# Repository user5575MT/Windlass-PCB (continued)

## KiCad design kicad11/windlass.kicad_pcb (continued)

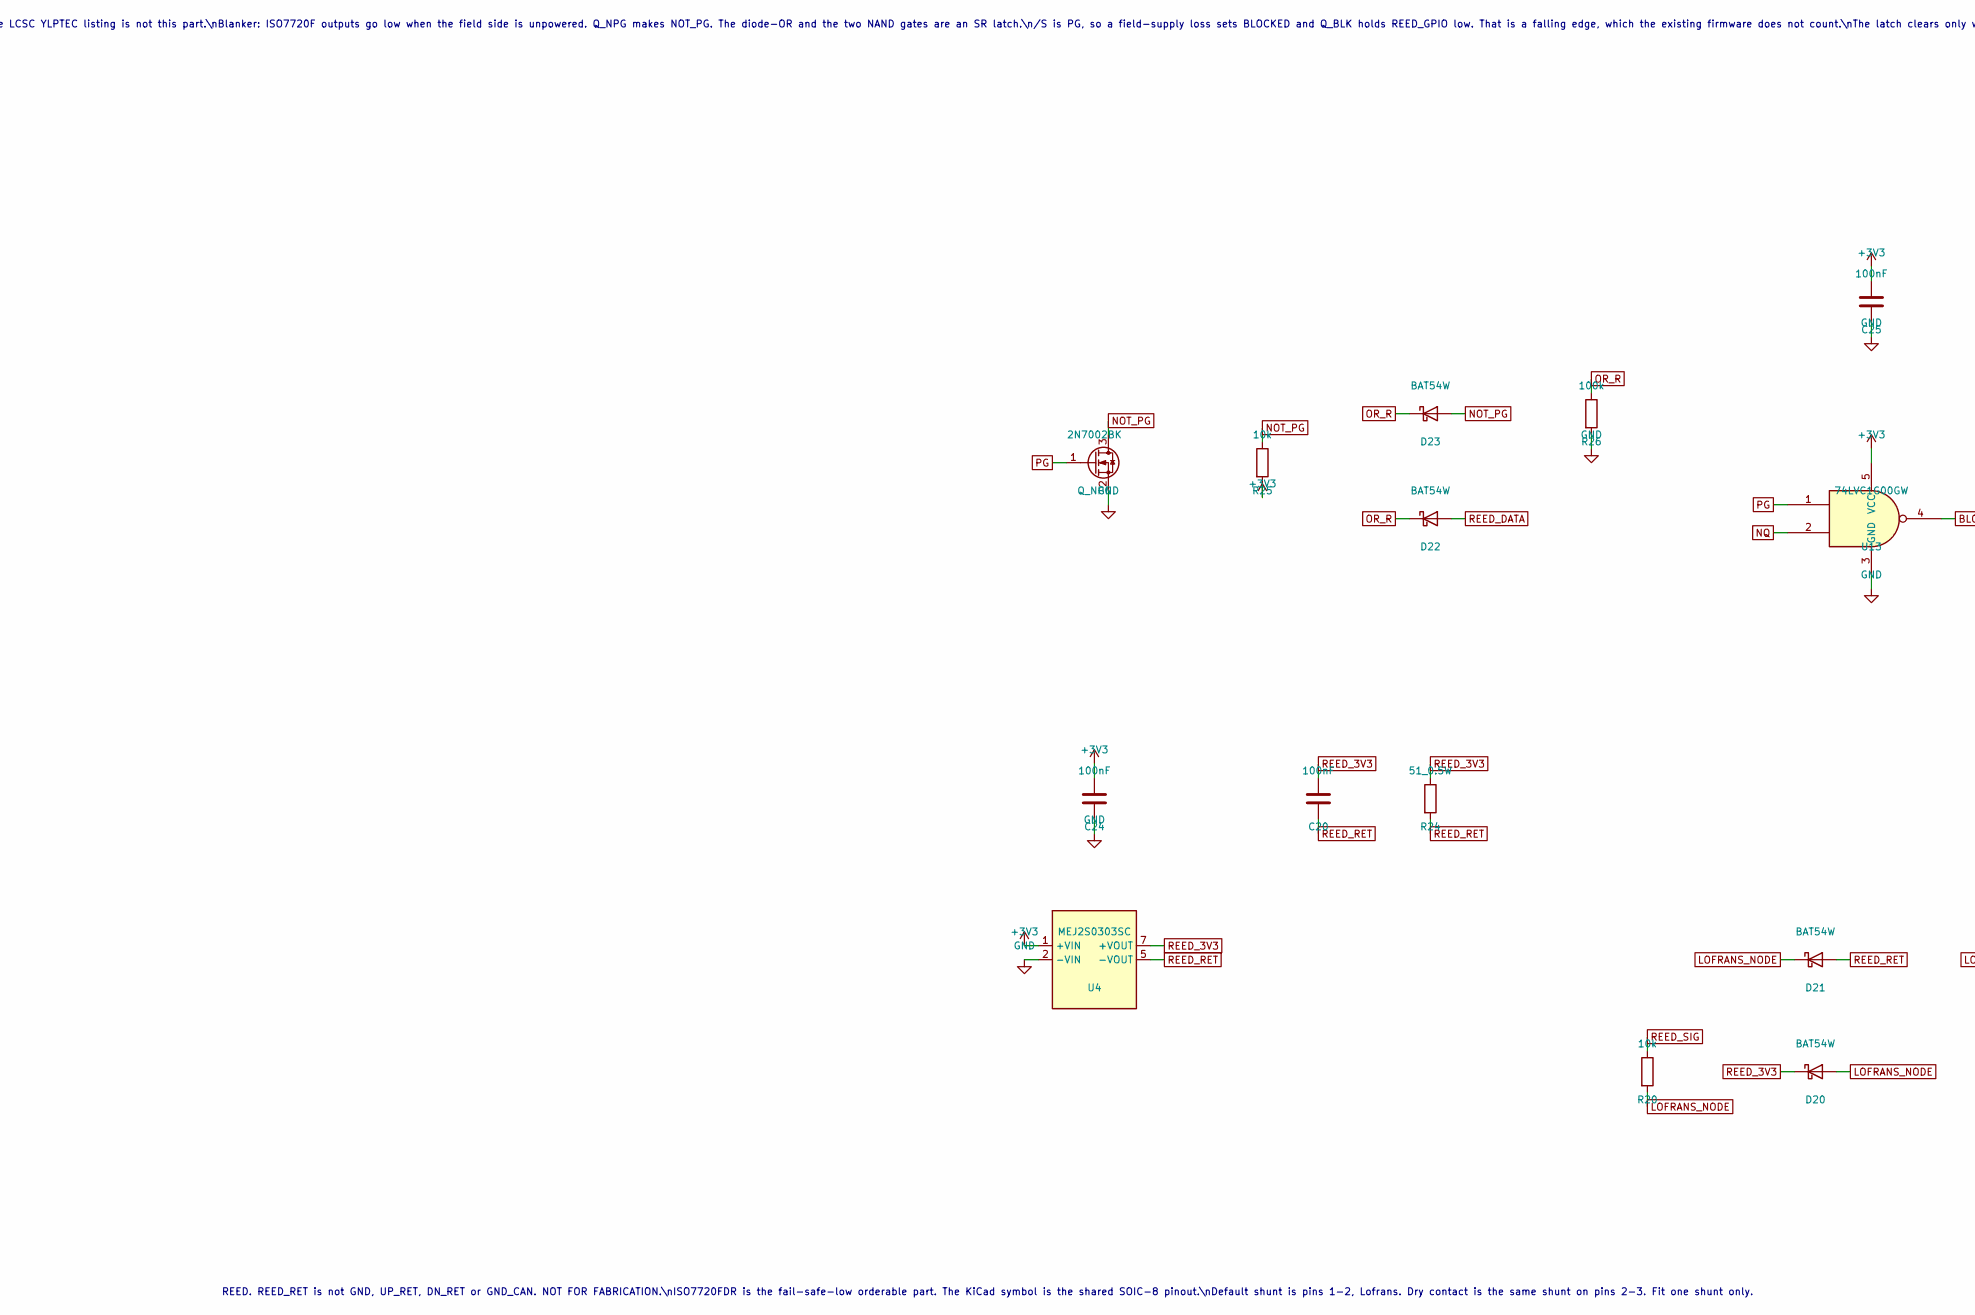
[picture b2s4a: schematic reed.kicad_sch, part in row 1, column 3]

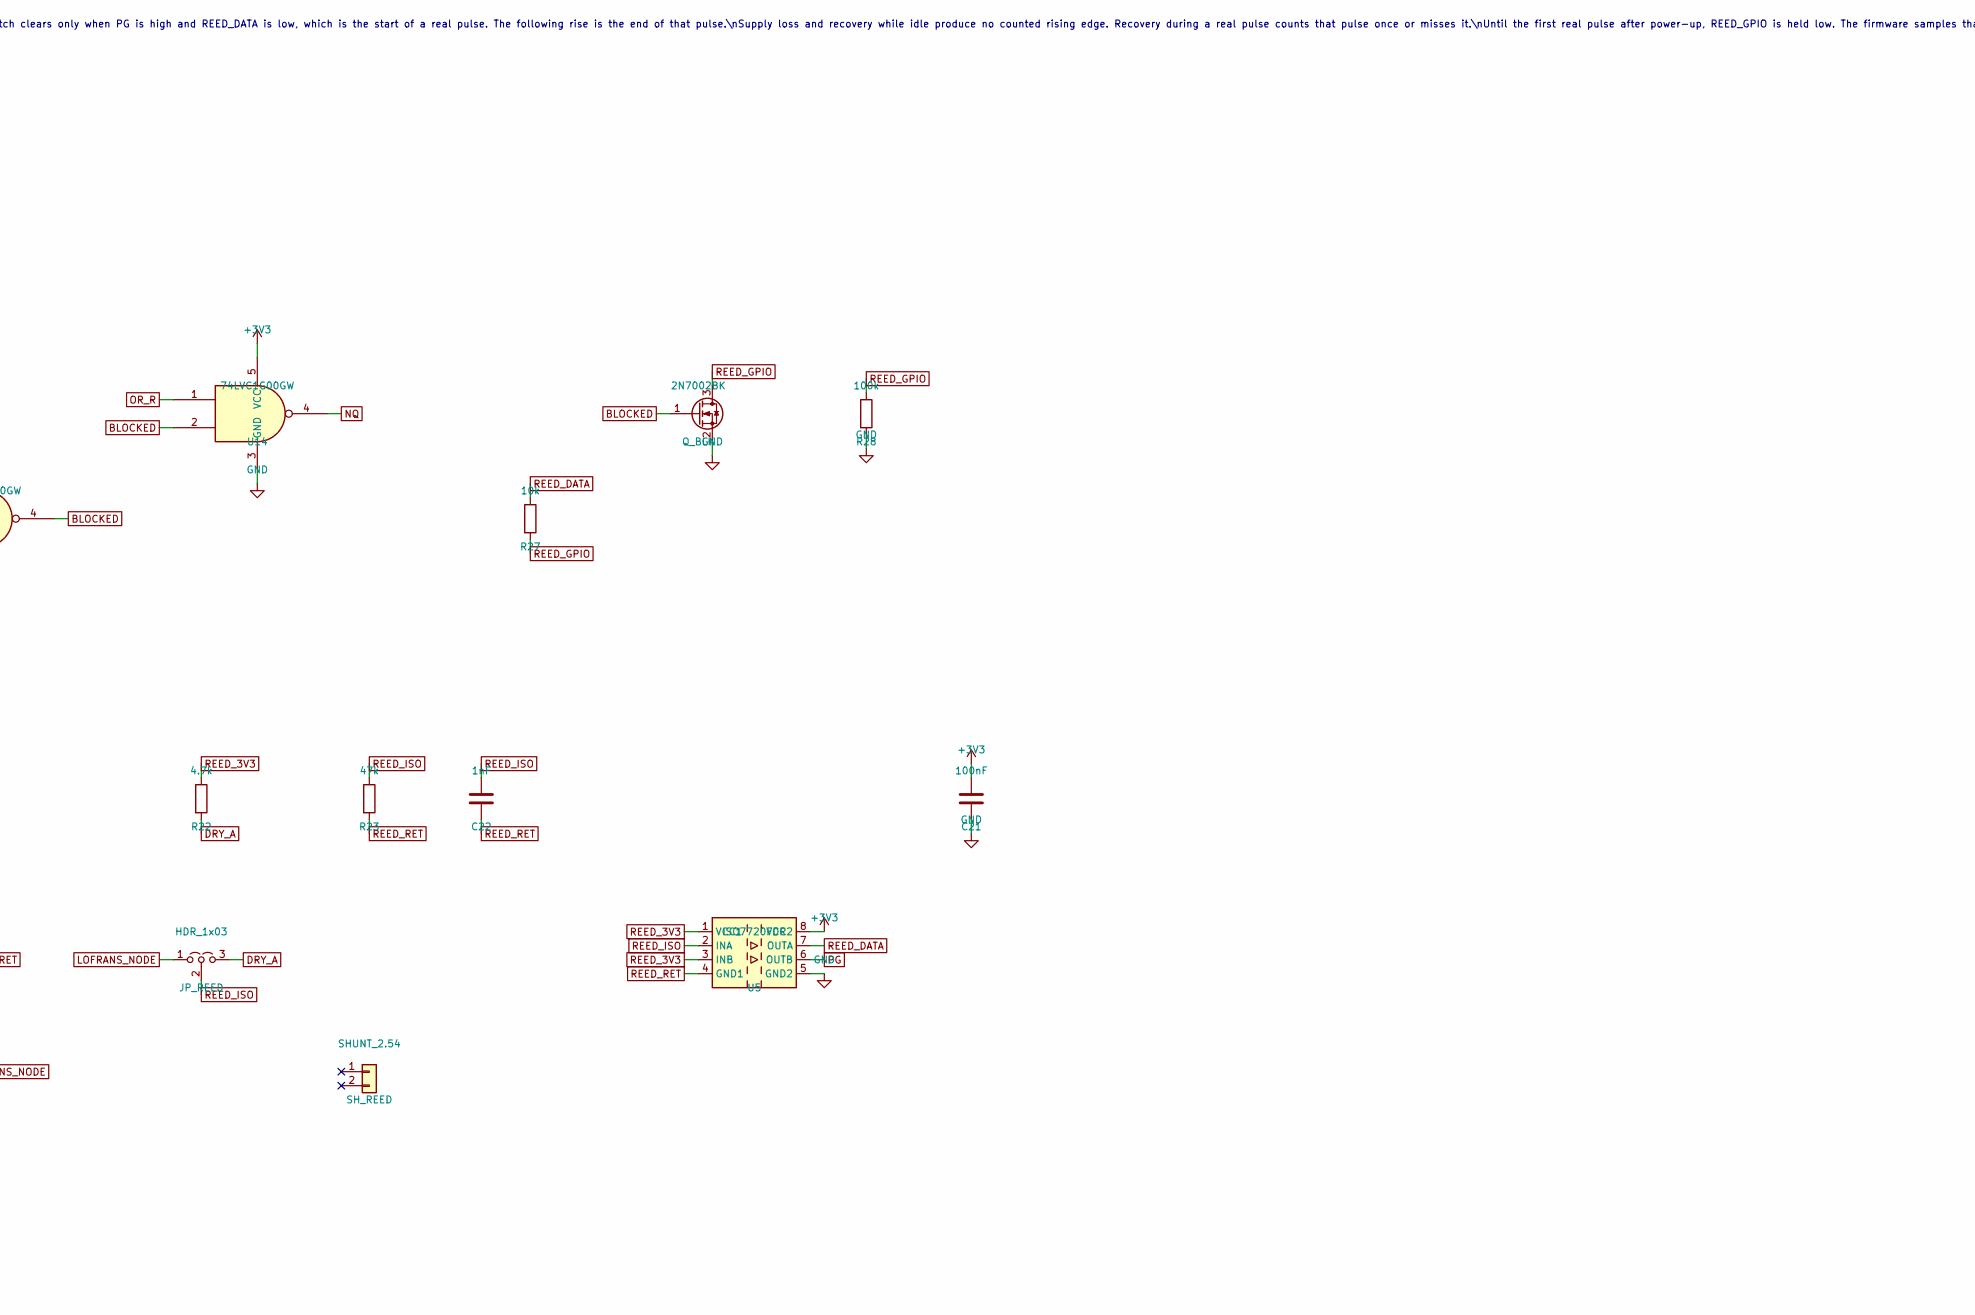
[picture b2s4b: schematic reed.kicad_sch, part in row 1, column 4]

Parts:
C20, C21, C24, C25: 100nF; C_0402_1005Metric
C22: 1nF; C_0402_1005Metric
D20, D21, D22, D23: BAT54W; D_SOD-123
JP_REED: HDR_1x03; PinHeader_1x03_P2.54mm_Vertical
Q_BLK: 2N7002BK; SOT-23
Q_NPG: 2N7002BK; SOT-23
R20, R25, R27: 10k; R_0402_1005Metric
R22: 4.7k; R_0402_1005Metric
R23: 47k; R_0402_1005Metric
R24: 51_0.5W; R_2512_6332Metric
R26, R28: 100k; R_0402_1005Metric
SH_REED: SHUNT_2.54
U4: MEJ2S0303SC; Murata_MEJ2SxxxxSC
U5: ISO7720FDR; SOIC-8_3.9x4.9mm_P1.27mm
U13, U14: 74LVC1G00GW; SOT-353_SC-70-5

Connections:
+3V3: C21.1, C24.1, C25.1, R25.2, U4.1 (+VIN), U5.8 (VCC2), U13.5 (VCC), U14.5 (VCC); also elsewhere on the board
BLOCKED: Q_BLK.1 (G), U13.4, U14.2
DRY_A: JP_REED.3 (B), R22.2; also elsewhere on the board
GND: C21.2, C24.2, C25.2, Q_BLK.2 (S), Q_NPG.2 (S), R26.2, R28.2, U4.2 (-VIN), U5.5 (GND2), U13.3 (GND), U14.3 (GND); also elsewhere on the board
LOFRANS_NODE: D20.2 (A), D21.1 (K), JP_REED.1 (A), R20.2
NOT_PG: D23.2 (A), Q_NPG.3 (D), R25.1
NQ: U13.2, U14.4
OR_R: D22.1 (K), D23.1 (K), R26.1, U14.1
PG: Q_NPG.1 (G), U5.6 (OUTB), U13.1
REED_3V3: C20.1, D20.1 (K), R22.1, R24.1, U4.7 (+VOUT), U5.1 (VCC1), U5.3 (INB)
REED_DATA: D22.2 (A), R27.1, U5.7 (OUTA)
REED_GPIO: Q_BLK.3 (D), R27.2, R28.1; also elsewhere on the board
REED_ISO: C22.1, JP_REED.2 (C), R23.1, U5.2 (INA)
REED_RET: C20.2, C22.2, D21.2 (A), R23.2, R24.2, U4.5 (-VOUT), U5.4 (GND1); also elsewhere on the board
REED_SIG: R20.1; also elsewhere on the board

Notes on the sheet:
REED. REED_RET is not GND, UP_RET, DN_RET or GND_CAN. NOT FOR FABRICATION.\nISO7720FDR is the fail-safe-low orderable part. The KiCad symbol is the shared SOIC-8 pinout.\nDefault shunt is pins 1-2, Lofrans. Dry contact is the same shunt on pins 2-3. Fit one shunt only.
Lofrans load is 3.3 V / 47k = 70 uA, and only while the shunt is on pins 1-2. The 4.7k pull-up is on DRY_A and cannot reach REED_SIG in that position.\nR20 is 10k in series. D20 and D21 clamp LOFRANS_NODE to the field 3.3 V rail. The Lofrans wire is not connected to an ESP32 pin.\nMEJ2S0303SC is 3.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

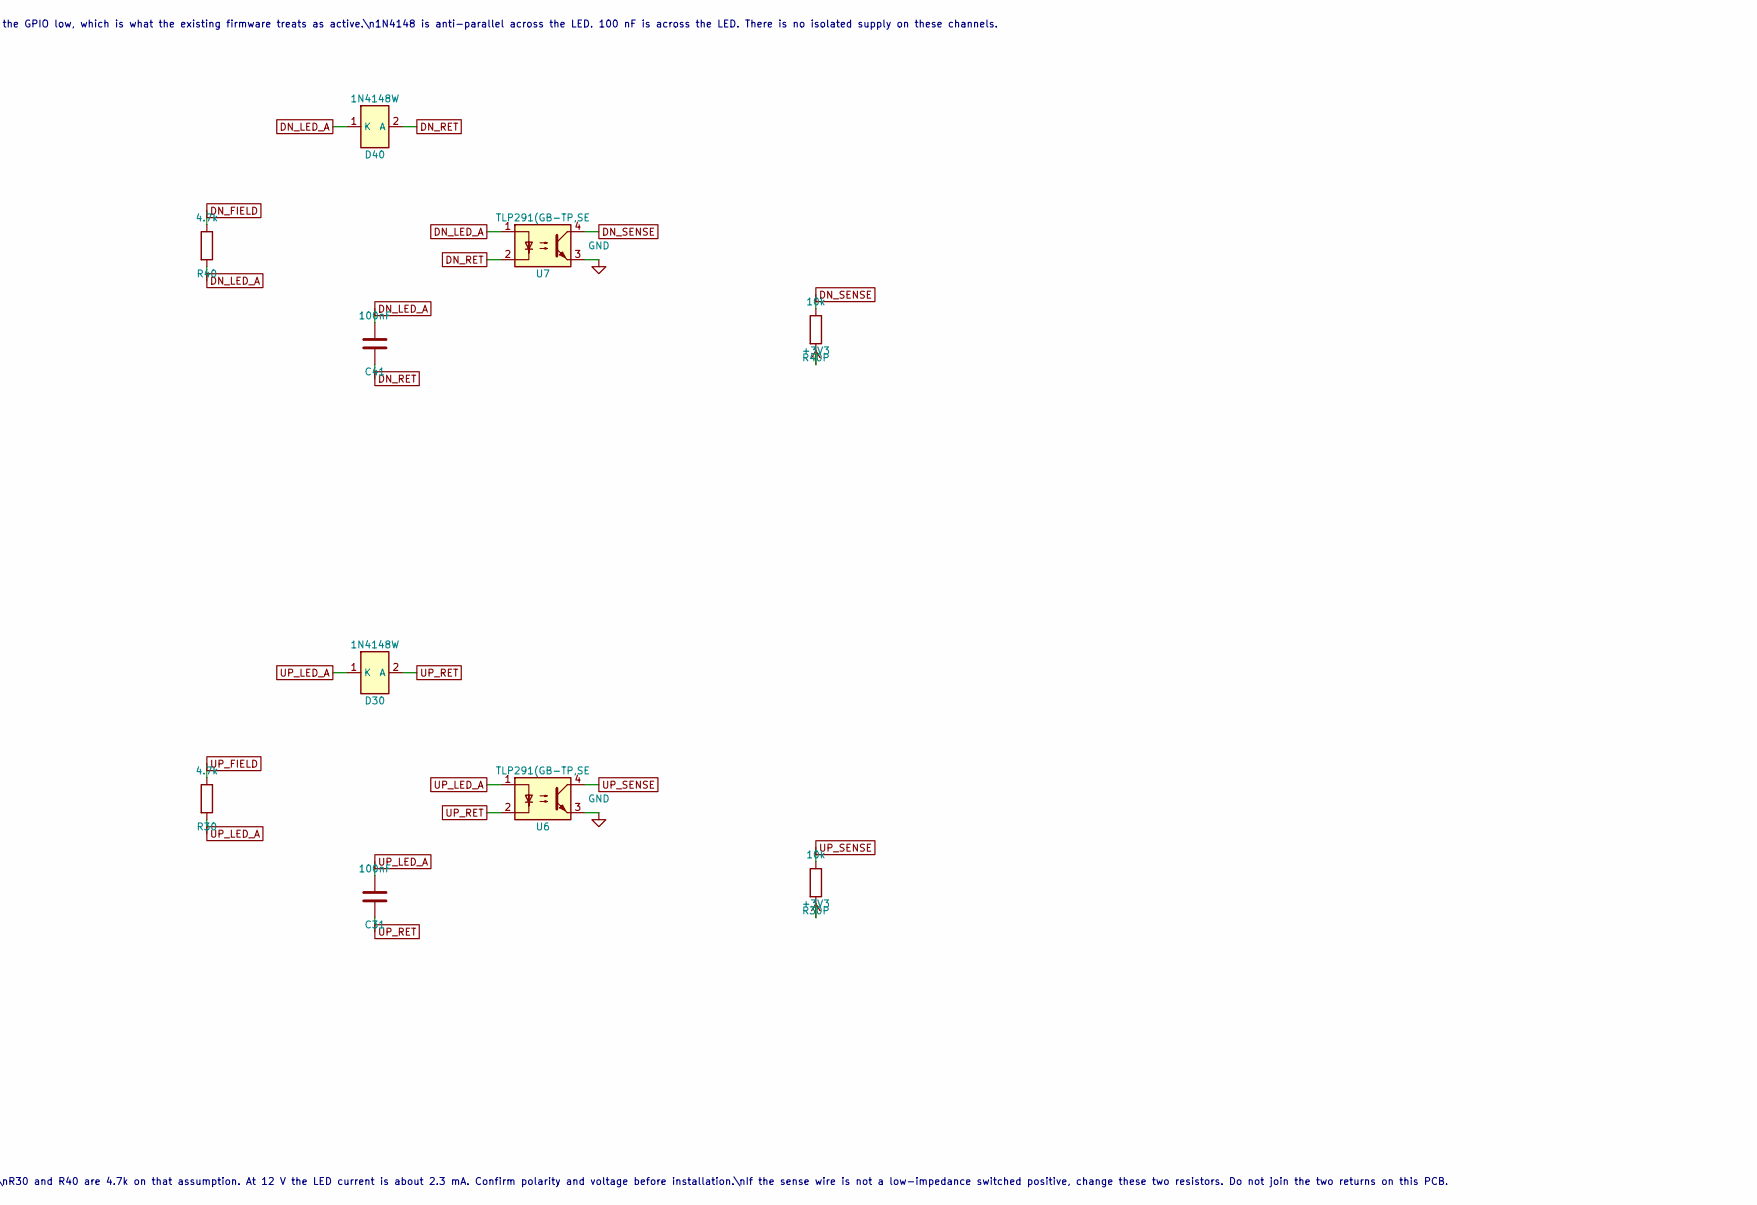
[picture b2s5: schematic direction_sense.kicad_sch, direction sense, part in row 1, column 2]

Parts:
C31, C41: 100nF; C_0402_1005Metric
D30, D40: 1N4148W; D_SOD-123
R30, R40: 4.7k; R_0402_1005Metric
R30P, R40P: 10k; R_0402_1005Metric
U6, U7: TLP291(GB-TP,SE; SOIC-4_4.55x2.6mm_P1.27mm

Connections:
+3V3: R30P.2, R40P.2; also elsewhere on the board
DN_FIELD: R40.1; also elsewhere on the board
DN_LED_A: C41.1, D40.1 (K), R40.2, U7.1
DN_RET: C41.2, D40.2 (A), U7.2; also elsewhere on the board
DN_SENSE: R40P.1, U7.4; also elsewhere on the board
GND: U6.3, U7.3; also elsewhere on the board
UP_FIELD: R30.1; also elsewhere on the board
UP_LED_A: C31.1, D30.1 (K), R30.2, U6.1
UP_RET: C31.2, D30.2 (A), U6.2; also elsewhere on the board
UP_SENSE: R30P.1, U6.4; also elsewhere on the board

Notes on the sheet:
DIRECTION SENSE. UP_RET and DN_RET are different nets. Neither joins GND. NOT FOR FABRICATION.\nAssumption, not a measurement: each FIELD pin is a switched positive voltage, about 5 V to 24 V, and the matching RET pin is that circuit's return.\nR30 and R40 are 4.7k on that assumption. At 12 V the L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
TLP291(GB-TP,SE): pin 1 anode, pin 2 cathode, pin 3 emitter, pin 4 collector.\nEmitter is board GND. Collector is the GPIO with a 10k pull-up to 3.3 V. LED on pulls the GPIO low, which is what the existing firmware treats as active.\n1N4148 is anti-parallel across the LED. 100 nF is across the LED.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

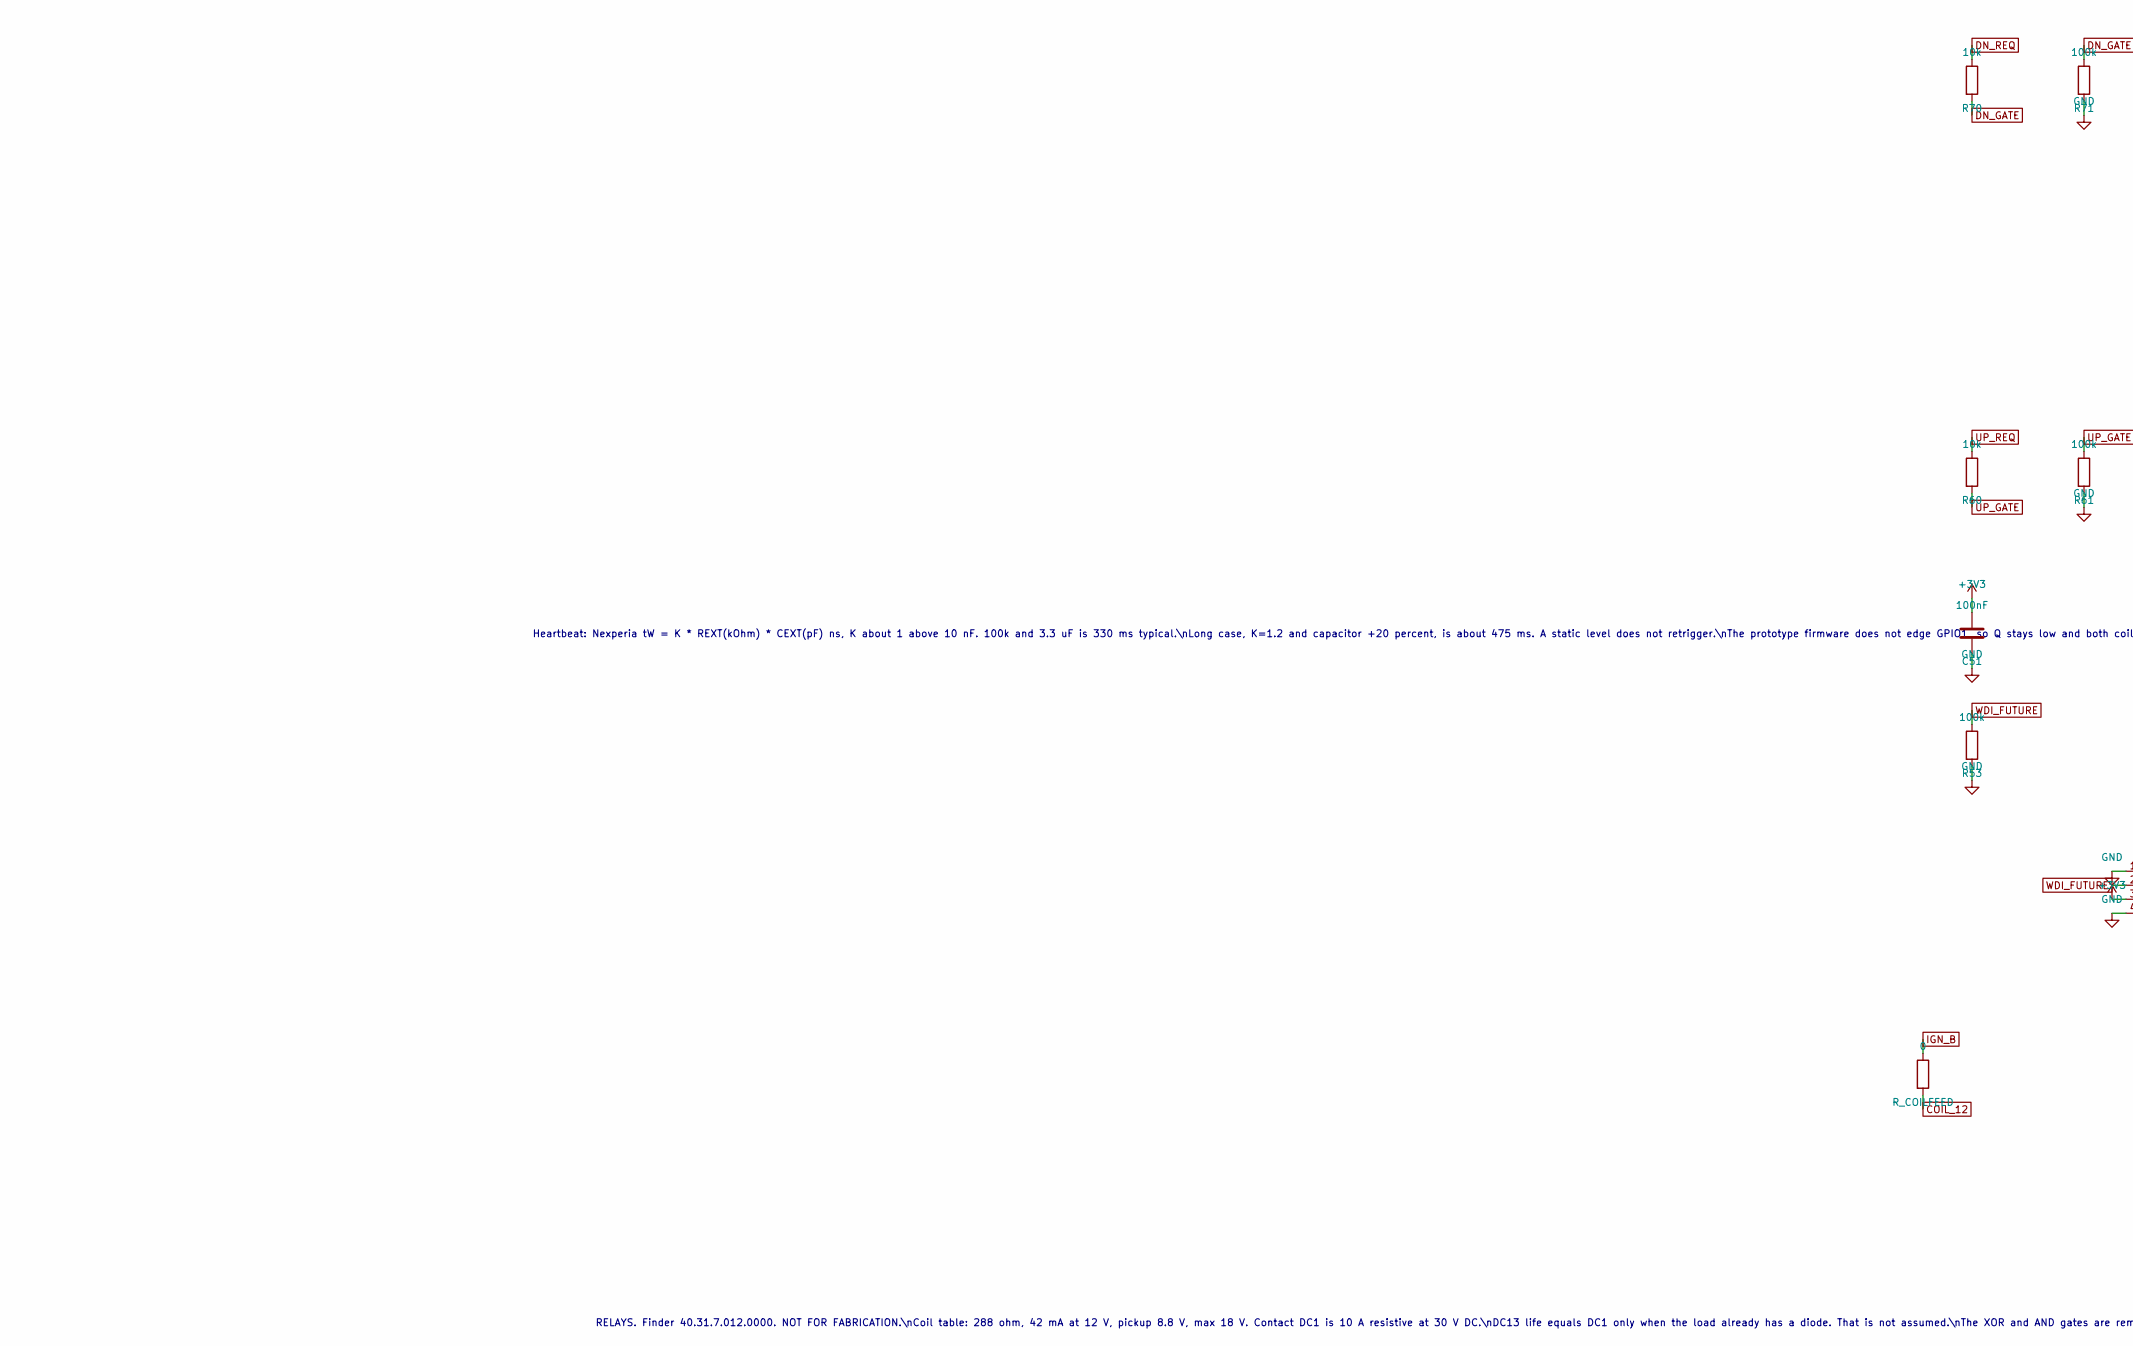
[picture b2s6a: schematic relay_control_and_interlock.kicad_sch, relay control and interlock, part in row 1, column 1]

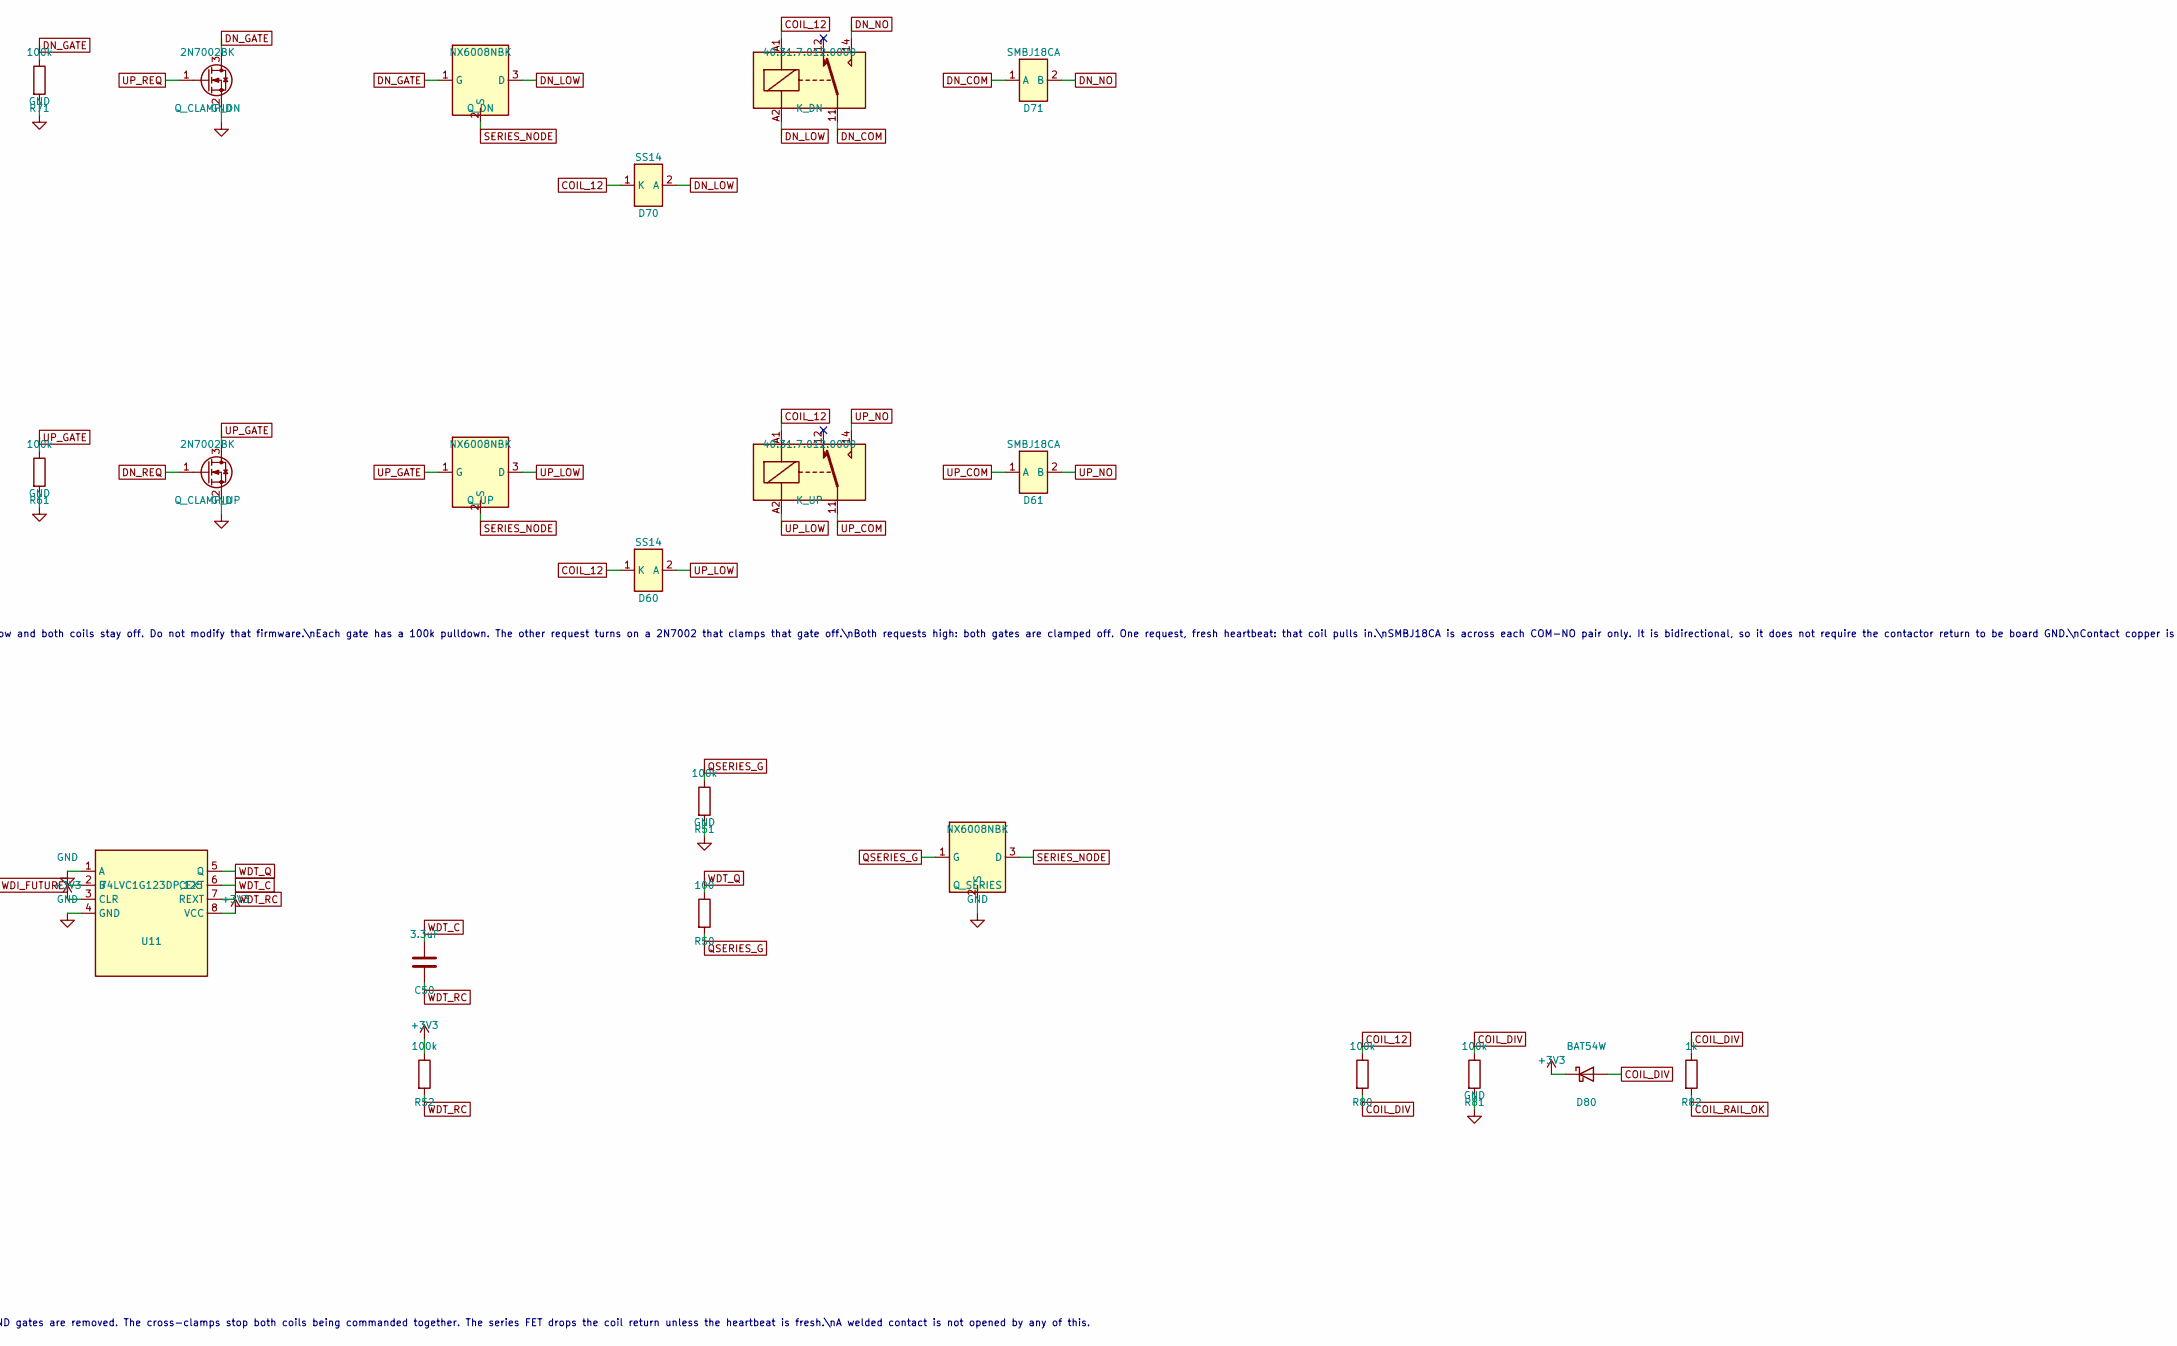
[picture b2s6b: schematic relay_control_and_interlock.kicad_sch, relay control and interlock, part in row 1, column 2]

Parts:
C50: 3.3uF; C_0805_2012Metric
C51: 100nF; C_0402_1005Metric
D60, D70: SS14; D_SMA
D61, D71: SMBJ18CA; D_SMB
D80: BAT54W; D_SOD-123
K_DN: 40.31.7.012.0000; Relay_SPDT_Finder_40.31
K_UP: 40.31.7.012.0000; Relay_SPDT_Finder_40.31
Q_CLAMP_DN: 2N7002BK; SOT-23
Q_CLAMP_UP: 2N7002BK; SOT-23
Q_DN: NX6008NBK; SOT-23
Q_SERIES: NX6008NBK; SOT-23
Q_UP: NX6008NBK; SOT-23
R50: 100; R_0402_1005Metric
R51, R52, R53, R61, R71, R80, R81: 100k; R_0402_1005Metric
R60, R70: 10k; R_0402_1005Metric
R82: 1k; R_0402_1005Metric
R_COILFEED: 0; R_0402_1005Metric
U11: 74LVC1G123DP,125; TSSOP-8_3x3mm_P0.65mm

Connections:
+3V3: C51.1, D80.1 (K), R52.1, U11.3 (CLR), U11.8 (VCC); also elsewhere on the board
COIL_12: D60.1 (K), D70.1 (K), K_DN.A1, K_UP.A1, R80.1, R_COILFEED.2
COIL_DIV: D80.2 (A), R80.2, R81.1, R82.1
COIL_RAIL_OK: R82.2; also elsewhere on the board
DN_COM: D71.1 (A), K_DN.11; also elsewhere on the board
DN_GATE: Q_CLAMP_DN.3 (D), Q_DN.1 (G), R70.2, R71.1
DN_LOW: D70.2 (A), K_DN.A2, Q_DN.3 (D)
DN_NO: D71.2 (B), K_DN.14; also elsewhere on the board
DN_REQ: Q_CLAMP_UP.1 (G), R70.1; also elsewhere on the board
GND: C51.2, Q_CLAMP_DN.2 (S), Q_CLAMP_UP.2 (S), Q_SERIES.2 (S), R51.2, R53.2, R61.2, R71.2, R81.2, U11.1 (A), U11.4 (GND); also elsewhere on the board
IGN_B: R_COILFEED.1; also elsewhere on the board
QSERIES_G: Q_SERIES.1 (G), R50.2, R51.1
SERIES_NODE: Q_DN.2 (S), Q_SERIES.3 (D), Q_UP.2 (S)
UP_COM: D61.1 (A), K_UP.11; also elsewhere on the board
UP_GATE: Q_CLAMP_UP.3 (D), Q_UP.1 (G), R60.2, R61.1
UP_LOW: D60.2 (A), K_UP.A2, Q_UP.3 (D)
UP_NO: D61.2 (B), K_UP.14; also elsewhere on the board
UP_REQ: Q_CLAMP_DN.1 (G), R60.1; also elsewhere on the board
WDI_FUTURE: R53.1, U11.2 (B); also elsewhere on the board
WDT_C: C50.1, U11.6 (CEXT)
WDT_Q: R50.1, U11.5 (Q)
WDT_RC: C50.2, R52.2, U11.7 (REXT)

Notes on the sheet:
RELAYS. Finder 40.31.7.012.0000. NOT FOR FABRICATION.\nCoil table: 288 ohm, 42 mA at 12 V, pickup 8.8 V, max 18 V. Contact DC1 is 10 A resistive at 30 V DC.\nDC13 life equals DC1 only when the load already has a diode. That is not assumed.\nThe XOR and AND gates are removed. The cross-clamps stop b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
Heartbeat: Nexperia tW = K * REXT(kOhm) * CEXT(pF) ns, K about 1 above 10 nF. 100k and 3.3 uF is 330 ms typical.\nLong case, K=1.2 and capacitor +20 percent, is about 475 ms. A static level does not retrigger.\nThe prototype firmware does not edge GPIO1, so Q stays low and both coils stay off. Do n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

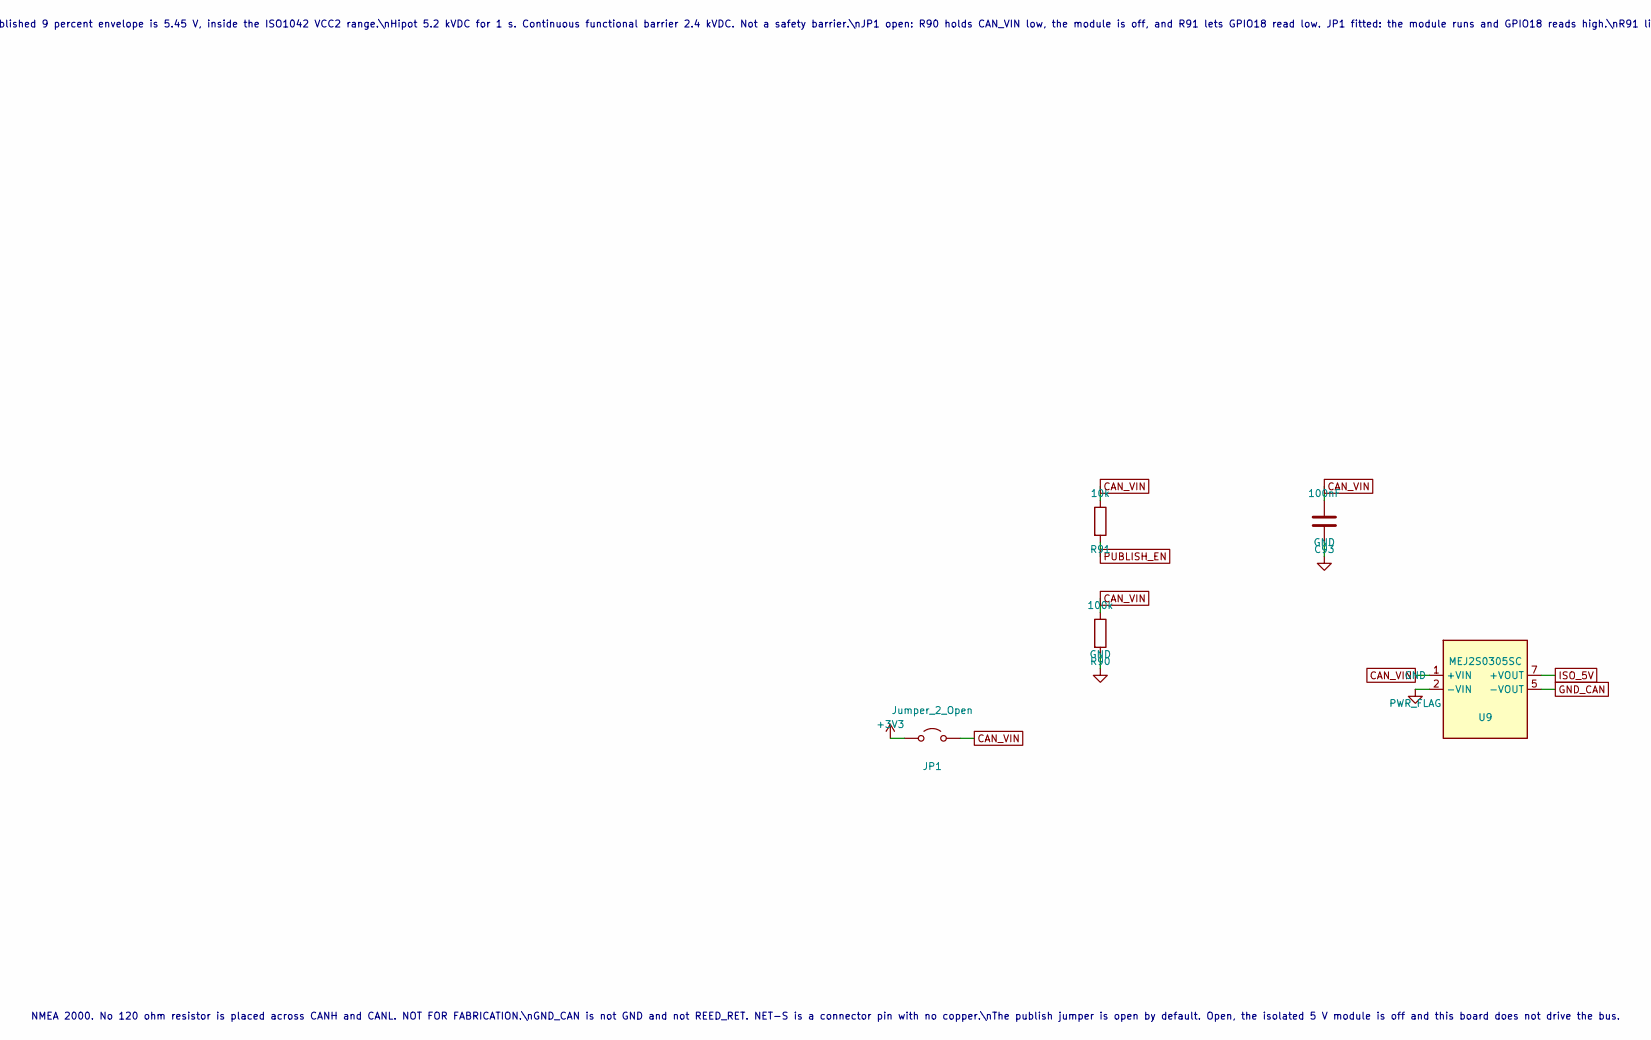
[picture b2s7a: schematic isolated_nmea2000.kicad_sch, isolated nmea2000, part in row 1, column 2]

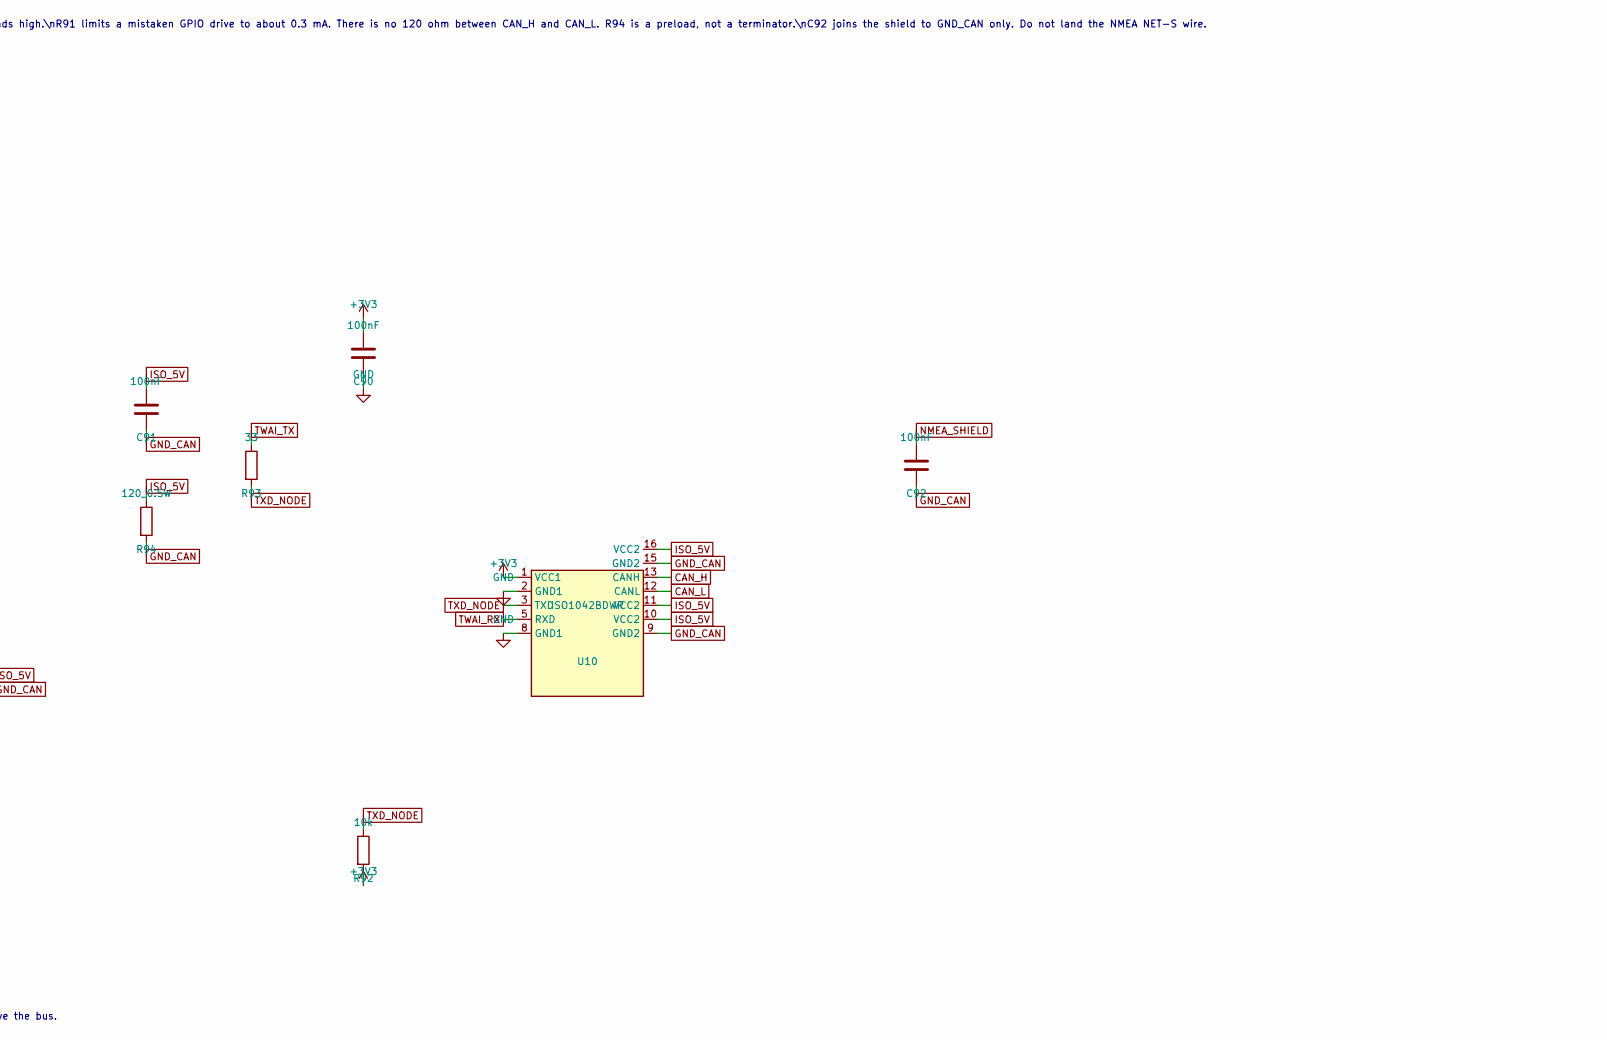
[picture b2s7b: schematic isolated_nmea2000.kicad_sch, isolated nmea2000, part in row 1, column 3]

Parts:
C90, C91, C92, C93: 100nF; C_0402_1005Metric
JP1: Jumper_2_Open; PinHeader_1x02_P2.54mm_Vertical
R90: 100k; R_0402_1005Metric
R91, R92: 10k; R_0402_1005Metric
R93: 33; R_0402_1005Metric
R94: 120_0.5W; R_2512_6332Metric
U9: MEJ2S0305SC; Murata_MEJ2SxxxxSC
U10: ISO1042BDWR; SOIC-16W_7.5x10.3mm_P1.27mm

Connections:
+3V3: C90.1, JP1.1 (A), R92.2, U10.1 (VCC1); also elsewhere on the board
CAN_H: U10.13 (CANH); also elsewhere on the board
CAN_L: U10.12 (CANL); also elsewhere on the board
CAN_VIN: C93.1, JP1.2 (B), R90.1, R91.1, U9.1 (+VIN)
GND: C90.2, C93.2, R90.2, U9.2 (-VIN), U10.2 (GND1), U10.8 (GND1); also elsewhere on the board
GND_CAN: C91.2, C92.2, R94.2, U9.5 (-VOUT), U10.9 (GND2), U10.15 (GND2); also elsewhere on the board
ISO_5V: C91.1, R94.1, U9.7 (+VOUT), U10.10 (VCC2), U10.11 (VCC2), U10.16 (VCC2)
NMEA_SHIELD: C92.1; also elsewhere on the board
PUBLISH_EN: R91.2; also elsewhere on the board
TWAI_RX: U10.5 (RXD); also elsewhere on the board
TWAI_TX: R93.1; also elsewhere on the board
TXD_NODE: R92.1, R93.2, U10.3 (TXD)

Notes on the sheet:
NMEA 2000. No 120 ohm resistor is placed across CANH and CANL. NOT FOR FABRICATION.\nGND_CAN is not GND and not REED_RET. NET-S is a connector pin with no copper.\nThe publish jumper is open by default. Open, the isolated 5 V module is off and this board does not drive the bus.
ISO1042 primary is 3.3 V. VCC2 must be 4.5 V to 5.5 V, so U9 is a Murata MEJ2S0305SC, 3.3 V to 5 V, 400 mA rating.\nR94 is 120 ohm, about 42 mA, just over 10 percent of that rating. 5 V plus the published 9 percent envelope is 5.45 V, inside the ISO1042 VCC2 range.\nHipot 5.2 kVDC for 1 s. Continuo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
